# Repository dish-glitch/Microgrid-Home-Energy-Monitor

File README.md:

# Home Energy Monitor

**A custom PCB that measures real-time household power consumption (Watts, apparent power (VA), and power factor) and streams live data to an OLED screen, a WiFi dashboard, and a Modbus TCP/IP server (the same protocol real industrial power meters use).**

---

## Schematic Preview

---

## PCB Preview

## Enclosure Preview

---

## What It Does

Non-invasive current transformer (CT) sensors clip around household wires inside a breaker box(does not touch any live wires). The custom PCB conditions the signal from the sensors and feeds it to an ESP32 microcontroller. The microcontroller then samples the voltage and current to compute:

- **Real Power (Watts)** 
- **Apparent Power (VA)**
- **Power Factor** 
- **Cumulative kWh** 

The readings come out three ways: a small OLED on the device, a live dashboard served over WiFi that you can open in any browser, and a Modbus TCP/IP server so industrial software like PLCs, SCADA, or Home Assistant can read the meter directly.

---

## How It Works

The SCT-013 current clamp outputs a small AC signal that mirrors the current in the wire it's clamped around. Before the ESP-32 is able to sample the signal, it must condition it. 

1. **It swings negative** — the ESP32 ADC only reads 0–3.3V. An op-amp bias circuit lifts the signal to a 1.65V midpoint so it never goes below 0V.
2. **It's in the wrong units** — a burden resistor converts current to a readable voltage via Ohm's Law (V = I × R).
3. **It carries noise** — an RC low-pass filter passes 60Hz but blocks high-frequency interference.

The ESP32 samples the signal and calculates RMS values in firmware and then uses those measurements to produce real power, apparent power, and power factor. 

---

## Modbus TCP/IP

I added a Modbus TCP server so this works more like a real industrial power meter instead of just a hobby project. Modbus is the protocol that commercial meters from companies like Schneider Electric and ABB use to send their readings to building systems and SCADA software. I got the idea from a PLC Dojo certification I finished on programming Modbus TCP clients and servers, and I wanted to actually use what I learned on my own hardware.

The ESP32 runs the Modbus server on port 502 at the same time as the web dashboard on port 80, so both run off the same WiFi. Any Modbus client, like a PLC, SCADA software, Home Assistant, Node-RED, or even a Python script, can read the meter by asking for its holding registers with Function Code 3.

Modbus registers can only hold 16-bit whole numbers, so I scale the decimal readings into whole numbers before writing them, and the client divides by the same number to get the real value back.

| Register | Modbus Address | Value | Scaling | Example |
|---|---|---|---|---|
| 0 | 40001 | Voltage (Vrms) | ×10 | `1200` → 120.0 V |
| 1 | 40002 | Current CH1 (Irms) | ×100 | `500` → 5.00 A |
| 2 | 40003 | Real Power CH1 (W) | ×1 | `600` → 600 W |
| 3 | 40004 | Apparent Power CH1 (VA) | ×1 | `650` → 650 VA |
| 4 | 40005 | Power Factor | ×100 | `92` → 0.92 |
| 5 | 40006 | Total Energy (kWh) | ×10 | `123` → 12.3 kWh |
| 6 | 40007 | Current CH2 (Irms) | ×100 | `300` → 3.00 A |
| 7 | 40008 | Real Power CH2 (W) | ×1 | `360` → 360 W |

> Register 0 in the code shows up as 40001 in most Modbus software. The 4xxxx numbering is just the standard way holding registers get labeled.

---

## Hardware

> Prices are what you actually pay per order, not per component. Amazon prices fluctuate — check links for current pricing. Order DigiKey items together to share one shipping fee (~$8 flat).

| Component | Ref | Need | What to Buy | Pack | Est. Order Price | Where |
|---|---|---|---|---|---|---|
| ESP32-WROOM-32 module | U1 | 1 | ESP-WROOM-32D 5-pack | 5 | ~$16 | [Amazon][(https://www.amazon.com/ESP-WROOM-32D-ESP-32-Bluetooth-Module-ESP32-WROOM-32D/dp/B085BNHPW5)](https://www.amazon.com/DORHEA-ESP-WROOM-32D-Bluetooth-integrates-ESP32-D0WD/dp/B08XXH9RMT/ref=sr_1_4?crid=1PAA57ZDBXXKA&dib=eyJ2IjoiMSJ9._MntEg_yRxGkBw1EfxLq6cc-w3Tk4YEgtB1QtlP6Z4yxtTF4Fgfk1zGfVmxLEI5m1rj4c-1jFTGRVePtGjaZB-u8IC_M2NuE5i72-Z6dyDMhy--t0tJ7uNgECgIogId0cCfDd5HPa67FyROcsTOtQSfSzK0LDP2i9msGrrE8LXcygPlws7SA2oZ1K6vlKAqsIRbaACC8jXyDBxBi5YwBBB_2cBgjYlD-LvbD8llQCdCVJK7sxuom2wjza4DP2pI0dcSs2QY-L5haReDtaOngVqGGzxCfWKOjql3sHXlfzxA.qUdqsXgRGlyqVaLIAANpF-NeytYFG2HdsdXi1yK_r4c&dib_tag=se&keywords=ESP-WROOM-32D%2BESP32%2B2.4GHz%2BDual-Mode%2BBluetooth%2Band%2BWiFi%2BLow%2BPower%2BModule&nsdOptOutParam=true&qid=1783296447&s=electronics&sprefix=esp-wroom-32d%2Besp32%2B2.4ghz%2Bdual-mode%2Bbluetooth%2Band%2Bwifi%2Blow%2Bpower%2Bmodule%2Celectronics%2C220&sr=1-4&th=1) |
| CT sensor SCT-013-000 (100A) | J1, J2 sensors | 2 | KOOBOOK 2-pack | 2 | ~$15 | [Amazon](https://www.amazon.com/KOOBOOK-SCT-013-000-Non-invasive-Current-Transformer/dp/B07S4G2Y27) |
| ZMPT101B voltage sensor module | J6 sensor | 1 | Single module | 1 | ~$8 | Amazon |
| Op-amp MCP6002 DIP-8 | U2 | 1 | Juried Engineering 1-pack | 1 | ~$4 | [Amazon](https://www.amazon.com/MICROCHIP-MCP6002-I-MCP6002-Operational-Amplifier/dp/B07GMWJ523) |
| Voltage regulator AMS1117-3.3 | U3 | 1 | 10-pack SOT-223 | 10 | ~$6 | [Amazon](https://www.amazon.com/AMS1117-3-3-LM1117-SOT-223-Voltage-Regulator/dp/B00Y5EKAU2) |
| SMD resistors 0603 (33Ω, 10kΩ, 4.7kΩ, 5.1kΩ, 150Ω) | R1–R14 | 14 total | 0603 assortment kit — covers all 5 values | 660pc / 33 values | ~$9 | [Amazon](https://www.amazon.com/660pcs-0603-Resistors-Assortment-Values/dp/B0CH2XD7JY) |
| SMD capacitors 0603+0805 (100nF, 10µF) | C1–C9 | 9 total | 0603/0805 assortment kit (10pF–22µF) | 960pc / 16 values | ~$10 | [Amazon](https://www.amazon.com/Capacitor-10pF-22uF-Multilayer-Capacitors-Assortment/dp/B094Z9V5KK) |
| 3.5mm audio jack SMT (CUI SJ-3523-SMT) | J1, J2 | 2 | Order 2 individually | 2 | ~$5 | [DigiKey](https://www.digikey.com/en/products/detail/same-sky-formerly-cui-devices/SJ-3523-SMT-TR/281297) |
| USB-C receptacle (GCT USB4085-GF-A) — optional, the board can be powered from a 5V bench supply | J4 | 1 | Order 1 individually | 1 | ~$1 | [DigiKey](https://www.digikey.com/en/products/detail/gct/USB4085-GF-A/9859662) |
| 3mm LED (red or green) | D1, D2 | 2 | 10-pack | 10 | ~$5 | [Amazon](https://www.amazon.com/3mm-Round-Top-Red-LED/dp/B017TR4XWW) |
| Tactile button 6×6×4.3mm THT | SW1, SW2 | 2 | 10-pack | 10 | ~$5 | [Amazon](https://www.amazon.com/6x6x4-3mm-Momentary-Tactile-Button-Through/dp/B00EDJYK46) |
| 2.54mm male pin headers (J3 4-pin, J5 6-pin, J6 3-pin) | J3, J5, J6 | 13 pins | 40-pin breakable strip (snap to length) | 10×40 strips | ~$6 | [Amazon](https://www.amazon.com/MCIGICM-Header-2-45mm-Arduino-Connector/dp/B07PKKY8BX) |
| SSD1306 OLED 0.96" I2C | J3 display | 1 | Single unit | 1 | ~$7 | [Amazon](https://www.amazon.com/SSD1306-Display-128x64-Driver-Screen/dp/B0GRGLP6WW) |
| CP2102 USB-to-UART programmer (to flash via J5) | — | 1 | HiLetgo CP2102 | 1 | ~$7 | [Amazon](https://www.amazon.com/HiLetgo-CP2102-Converter-Adapter-Downloader/dp/B00LODGRV8) |
| PCB fabrication | — | 1 run | JLCPCB 5 boards + shipping | 5 boards | ~$20 | [JLCPCB](https://jlcpcb.com) |
| Enclosure | — | 1 | 3D printed PETG-CF | — | $0 | filament on hand |
| DigiKey shipping | — | — | Flat rate (order SJ-3523 + USB4085 together) | — | ~$8 | — |
| **Total** | | | | | **~$132** | |

---

## Repository Structure

```
home-energy-monitor/
├── hardware/        # KiCad schematic, PCB layout, Gerber files
├── firmware/        # ESP32 Arduino code (energy-monitor + board-test bring-up sketch)
├── enclosure/       # FreeCAD source + STL files for 3D printing
└── docs/
    └── photos/      # Build progress photos
```

---

## Build Log

| Date | Milestone |
|---|---|
| June 10, 2026 | Project started. Repository initialized. |
| June 11, 2026 | KiCad schematic started — analog front-end both CT channels complete |
| June 13, 2026 | KiCad schematic complete — ERC passes clean, all components wired |
| June 14, 2026 | PCB layout complete — all components placed, routed, ground plane poured, DRC clean |
| June 14, 2026 | Gerbers exported and committed — ready for JLCPCB upload |
| June 14, 2026 | Firmware written — RMS sampling, power math, OLED display, kWh accumulator. Verified on Wokwi simulator. |
| June 15, 2026 | WiFi dashboard complete — ESP32 serves live readings over HTTP, JavaScript polls every second |
| June 16, 2026 | 3D enclosure designed by [@hummos430](https://github.com/hummos430) in Fusion 360 — files committed |
| June 16, 2026 | Stardance funding submitted — S tier $150 |
| July 3, 2026 | DRC audit fixes — solid B.Cu ground plane added, ESP32 thermal via drills fixed, USB-C clearance rule corrected. ERC + DRC verified 0 errors. Gerbers re-exported — board ready to order |
| July 8, 2026 | Modbus TCP/IP server added — ESP32 exposes 8 holding registers on port 502, runs alongside the web dashboard |
| — | PCBs ordered from JLCPCB and received |
| Oct 22, 2026 | Board assembly started — SMD parts with solder paste on a mini hot plate, THT by hand |
| Oct 23, 2026 | First power-up. Tracked a 3.3V rail "short" down to 10Ω resistors (marked `01X`) fitted where the 10kΩ bias resistors (`01C`) belong — replaced them, rail came up at 3.3V. ESP32 boots and flashes over the J5 header |
| Oct 28, 2026 | Op-amp replaced (bench-tested on a breadboard first) and a bodge wire added for a damaged U2 pin 5 pad. Both CT channels verified at the 1.65V bias point, OLED found on I2C, full firmware running on the board |
| Nov 10, 2026 | CT jacks fitted (plug bodies trimmed to clear the PCB). First real current measurements with `SIMULATION 0`: a 300 W rice cooker read **2.40 A** on Cook against 2.50 A expected (300 W ÷ 120 V), within 4% before calibration. ICAL tuned 60.6 → 63.1. A desk fan read ~0.2 A; the noise floor with nothing on is ~0.12 A |
| — | ZMPT101B mains side enclosed, VCAL calibrated, real watts + power factor |
| — | Dashboard live, full system working |

---

## Build Photos

The assembled board running the real firmware (still in `SIMULATION 1` mode until the CT jacks and voltage sensor are connected) — OLED live, power LED and status LED on:

| First power-up | 5V bench supply, constant-voltage mode |
|---|---|
|  |  |

**Bring-up test** ([`firmware/board-test`](firmware/board-test/board-test.ino)) — the OLED answers on I2C, and both CT channels sit at the 1.65V bias midpoint with no clamp plugged in:

WiFi dashboard served by the ESP32 (port 80), viewed in a laptop browser on the same network:

Modbus TCP read from a laptop using [`tools/modbus_read.py`](tools/modbus_read.py) (Function Code 3, holding registers 40001–40008):

```
Raw registers: (1200, 500, 550, 600, 92, 0, 300, 360)
----------------------------------
Voltage:         120.0 V
Current CH1:     5.00 A
Real Power CH1:  550 W
Apparent CH1:    600 VA
Power Factor:    0.92
Total Energy:    0.0 kWh
Current CH2:     3.00 A
Real Power CH2:  360 W
```

*(Total energy is stored ×10, so it reads 0.0 until the running total passes 0.1 kWh.)*

Firmware serial output — readings every loop, kWh accumulating:

ESP32 boot log over the J5 programming header:

---

## Simulation

Test the firmware logic without hardware — runs in browser:

Simulates dual CT sensor readings, RMS power math, serial output, and OLED display on a virtual ESP32. CH1 uses test values (120V, 5A, 550W, PF 0.92) to verify the signal chain and kWh accumulator logic.

---

## Status

- [x] KiCad schematic — ERC clean (0 errors)
- [x] PCB layout — DRC clean (0 violations, 0 unconnected); B.Cu ground plane added
- [x] Gerbers exported from the DRC-clean board — ready for JLCPCB upload
- [x] Firmware — ADC sampling + RMS math
- [x] Firmware — power factor calculation
- [x] PCB fabrication (JLCPCB)
- [x] Board assembly + bring-up — power, ESP32, both CT channels, OLED verified
- [x] 3D enclosure design
- [x] WiFi dashboard
- [x] Modbus TCP/IP server (8 holding registers, Function Code 3)
- [x] CT jacks (J1/J2) fitted
- [x] Current calibration (ICAL) against a known resistive load
- [ ] ZMPT101B mains side enclosed + voltage calibration (VCAL)
- [ ] Full system test

---

## Acknowledgements

- **[@hummos430](https://github.com/hummos430)** — Designed and 3D printed the enclosure in Fusion 360
- **[Claude (Anthropic)](https://claude.ai)** — Claude was used to help document this project. I often recorded voice notes describing my engineering ideas, design decisions, and progress, then used Claude to organize those notes into structured GitHub documentation and tables. It also helped review the BOM and sanity-check component selections for consistency. The schematic, PCB layout, firmware, testing, and engineering decisions are my own.

---

## License

MIT — use, modify, share freely. See [LICENSE](LICENSE).

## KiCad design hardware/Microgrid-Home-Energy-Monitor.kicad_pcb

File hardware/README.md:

# Hardware

Custom 2-layer PCB designed in KiCad 9. Measures real-time household power consumption using non-invasive current transformer sensors.

---

## PCB Specifications

| Spec | Value |
|---|---|
| Layers | 2 (F.Cu / B.Cu) |
| Board dimensions | ~130mm × 75mm |
| Min trace width | 0.2mm signal / 0.4mm power |
| Min clearance | 0.15mm (accommodates the USB-C footprint's pad spacing; JLCPCB handles down to 0.127mm) |
| Copper pour | GND flood on F.Cu + solid GND plane on B.Cu, joined by stitching vias |
| Via drill | 0.3mm min |
| Surface finish | HASL (lead-free) |
| Fabrication | JLCPCB |

---

## Design Overview

### Power Path
USB-C (5V VBUS) → AMS1117-3.3 linear regulator → 3.3V rail → ESP32 + all peripherals

CC1 and CC2 resistors (5.1kΩ to GND) identify the board as a USB device to the host charger, enabling 5V/500mA delivery per USB-C spec.

### CT Sensor Signal Conditioning (per channel)
Each channel processes the AC output of an SCT-013-000 current transformer:

```
SCT-013 → 33Ω burden resistor → 10µF coupling cap → MCP6002 op-amp buffer → ESP32 ADC
                                    ↑
                          10kΩ/10kΩ bias divider (1.65V midpoint)
```

1. **Burden resistor (33Ω):** The SCT-013 outputs a small currecnt but the ESP32 measures the voltage. The 33 ohm burden resisotr converts that currecnt into a voltage using Ohm's law. At the senors's max rated current, this produeces 1.65 V RMS 2.33 V peak. 

2. **Bias divider (2× 10kΩ):** Becuase the ESP32 ADC can't read negative voltages, 2 10k ohm resistors create a 1.65 V bais point.
3. **Coupling capacitor (10µF):** Blocks DC from the burden resistor, and passes the 60Hz AC signal.
4. **MCP6002 buffer:** Unity-gain op-amp buffer to keep the bais network independent from the ESP32 ADC. Its high imput impedance prevents the bais voltage from shifting. 

### Voltage Sensing
ZMPT101B voltage transformer connects to J6. its output is routed to GPIO36 which is an input-only ADC pin with no internal pull resistors, chosen to minimize noise on the analog signal.

### I2C Bus
SDA (GPIO21) and SCL (GPIO22) pulled up to 3.3V via 4.7kΩ resistors. Pull-up value chosen for standard-mode I2C (100 kHz) with expected bus capacitance under 50pF.

### ESP32 Boot Circuit
- EN pulled high via 10kΩ (R7) + 100nF to GND for clean power-on reset
- GPIO0 held high by the ESP32's internal pull-up; SW2 pulls GPIO0 low for bootloader entry (R10 was meant as an external pull-up, but rev 1 wires it EN ↔ GPIO0 — leave it unfitted, see Assembly Notes)
- SW1 pulls EN low for hard reset

---

## Schematic

See [`Microgrid-Home-Energy-Monitor.kicad_sch`](Microgrid-Home-Energy-Monitor.kicad_sch)

---

## PCB Layout

See [`Microgrid-Home-Energy-Monitor.kicad_pcb`](Microgrid-Home-Energy-Monitor.kicad_pcb)

Key layout decisions:
- Analog front-end (J1, J2, U2, bias resistors) grouped bottom-right, away from ESP32 WiFi antenna
- ESP32 antenna overhangs the keepout zone — no copper pour under antenna area
- AMS1117 decoupling caps (C3–C6) placed within 2mm of regulator pins
- ESP32 VDD decoupling (C7, C8) placed directly below VDD pin
- USB-C connector (J4) edge-mounted on right wall for direct cable access
- Ground pour floods entire F.Cu layer

---

## Bill of Materials

| Ref | Component | Value | Package | MPN | Supplier |
|---|---|---|---|---|---|
| U1 | ESP32-WROOM-32 | — | Module | ESP32-WROOM-32E-N4 | Mouser 356-ESP32WROOM32EN4 |
| U2 | MCP6002 Op-Amp | — | DIP-8 | MCP6002-I/P | Digikey MCP6002-I/P-ND |
| U3 | AMS1117-3.3 | 3.3V LDO | SOT-223 | AMS1117-3.3 | Digikey 1665-1016-1-ND |
| J1, J2 | CT Sensor Input | 3.5mm jack | SMD | SJ-3523-SMT | Digikey CP-3523SJCT-ND |
| J3 | OLED Connector | 4-pin | 2.54mm header | — | generic |
| J4 | USB-C Receptacle (optional, see notes) | USB 2.0 | THT 16P | GCT USB4085-GF-A | Digikey 2073-USB4085-GF-ACT-ND |
| J5 | Programming Header | 6-pin | 2.54mm header | — | generic |
| J6 | ZMPT101B Connector | 3-pin | 2.54mm header | — | generic |
| R1, R4 | Burden Resistor (CH1, CH2) | 33Ω 1% | 0603 | — | generic |
| R2, R3, R5, R6 | Bias Resistor (R2/R3 CH1, R5/R6 CH2) | 10kΩ | 0603 | — | generic |
| R7 | EN Pull-up | 10kΩ | 0603 | — | generic |
| R8, R9 | I2C Pull-up | 4.7kΩ | 0603 | — | generic |
| R10 | GPIO0 Pull-up — **do not fit on rev 1**, see notes | 10kΩ | 0603 | — | generic |
| R11, R12 | CC Pull-down (only needed with J4) | 5.1kΩ | 0603 | — | generic |
| R13, R14 | LED Current Limit | 150Ω | 0603 | — | generic |
| C1, C2 | Coupling Cap | 10µF | 0805 | — | generic |
| C3, C6 | LDO Bulk Cap | 10µF | 0805 | — | generic |
| C4, C5 | LDO Bypass Cap | 100nF | 0603 | — | generic |
| C7 | ESP32 Bypass | 100nF | 0603 | — | generic |
| C8 | ESP32 Bulk | 10µF | 0805 | — | generic |
| C9 | EN Filter Cap | 100nF | 0603 | — | generic |
| D1 | Power LED | Red | 3mm THT | — | generic |
| D2 | Status LED | Green | 3mm THT | — | generic |
| SW1 | Reset Button | — | 6mm THT | — | generic |
| SW2 | Boot Button | — | 6mm THT | — | generic |
| CT1, CT2 | CT Sensor | SCT-013-000 | Clamp | SCT-013-000 | Amazon/AliExpress |
| VT1 | Voltage Sensor Module (plugs into J6) | ZMPT101B | Module | ZMPT101B | Amazon/AliExpress |

---

## Assembly Notes (rev 1)

Lessons from assembling the first board (solder paste + hot plate for SMD, iron for THT):

- **Read the 0603 resistor markings.** The 10kΩ bias resistors are marked **`01C`** (EIA-96) or **`103`**. A part marked **`01X`** is **10Ω** — fitting those in R2/R3/R5/R6 puts two 20Ω paths across the 3.3V rail and looks exactly like a short (supply drops into CC, the resistors near U2 get warm).
- **R10 — do not fit.** The BOM calls it a GPIO0 pull-up, but on the rev 1 PCB it is wired **EN ↔ GPIO0**, which drags GPIO0 low whenever RESET is pressed and can drop the ESP32 into download mode. The ESP32's internal pull-up on GPIO0 is enough, and SW2 still pulls it low to flash. *Fix for rev 2: connect R10 between GPIO0 and +3.3V.*
- **J1/J2 sit too far in from the board edge.** The SCT-013's molded plug body hits the PCB before the plug seats fully, and the plug's metal collar scrapes the solder mask in front of each jack. On rev 1, trim about 1–2 mm off the underside of each plug body (sandpaper or a file, not a soldering iron), seal any exposed wire with nail polish or CA glue, and protect the board in front of the jacks with Kapton tape. *Fix for rev 2: move J1/J2 so their openings are flush with, or slightly past, the board edge.*
- **J2 is CH1 and J1 is CH2.** J2 feeds R1/C1 → GPIO34 (`PIN_CT1`, real power + PF), J1 feeds R4/C2 → GPIO35 (`PIN_CT2`). Plug the clamp for the main load into **J2**.
- **J4 (USB-C) is optional.** It is power-only (D+/D− are not connected). Without it, power the board from a 5V bench supply into the J4 **VBUS** and **GND** holes or **TP1 (VBUS) / TP3 (GND)**, and leave R11/R12 off. In each J4 row the outermost small hole is GND and the next one in is VBUS; the four large oval slots are the shield and are **not** connected.
- **U2 orientation:** pin 1 is the **square pad**, at the notch end next to **TP2**. A socket is worth it — the chip is easy to damage when desoldering.
- **Do the SMD reflow before any THT parts** — headers, buttons and LEDs have plastic that will not survive the hot plate.
- **Programming:** J5 needs only 3 wires to a CP2102 — GND→pin 1, TXD→pin 4 (RX0), RXD→pin 3 (TX0). Leave the adapter's 3V3/5V unconnected when the board has its own supply. There is no auto-reset circuit: hold **BOOT (SW2)**, tap **RESET (SW1)**, release BOOT, upload, then press RESET.
- **OLED pin order:** many SSD1306 modules are **GND, VCC, SCL, SDA**, while J3 is **3.3V, GND, SCL, SDA**. Wire by label with jumpers instead of plugging the module straight in.

### Bring-up checklist

| Check | Expected |
|---|---|
| TP2 (3.3V) ↔ TP3 (GND), continuity, unpowered | **No beep** |
| 5V supply, ESP32 with factory firmware | CV, ~0.11 A, D1 lit |
| TP2 | 3.3V |
| [`board-test`](../firmware/board-test/board-test.ino) sketch, no sensors connected | CT1 ≈ CT2 ≈ **1650 mV** (bias midpoint), D2 blinking, BOOT button reported |
| OLED on J3 | I2C scan finds **0x3C** |

---

## Design Verification

All fixes from the 2026-07-02 DRC audit are complete (verified with `kicad-cli`):

- **ERC: 0 errors.** **DRC: 0 violations, 0 unconnected items.**
- GND split-pour islands eliminated by adding a solid B.Cu ground plane with stitching
  vias — front pour fragments all tie to it, so pinch-offs can't strand a ground pin
- ESP32 thermal vias enlarged to 0.3mm drill (JLCPCB 2-layer minimum)
- Minimum clearance set to 0.15mm to fit the USB-C footprint's actual pad spacing

---

## Fabrication Files

Gerber files for JLCPCB are in [`gerbers/`](gerbers/) — exported from the DRC-clean board, **ready to upload**.

JLCPCB order settings:
- Layers: 2
- Dimensions: per gerber
- PCB Qty: 5
- PCB Color: Black
- Surface Finish: HASL(lead-free)
- Copper Weight: 1oz
- All other settings: default

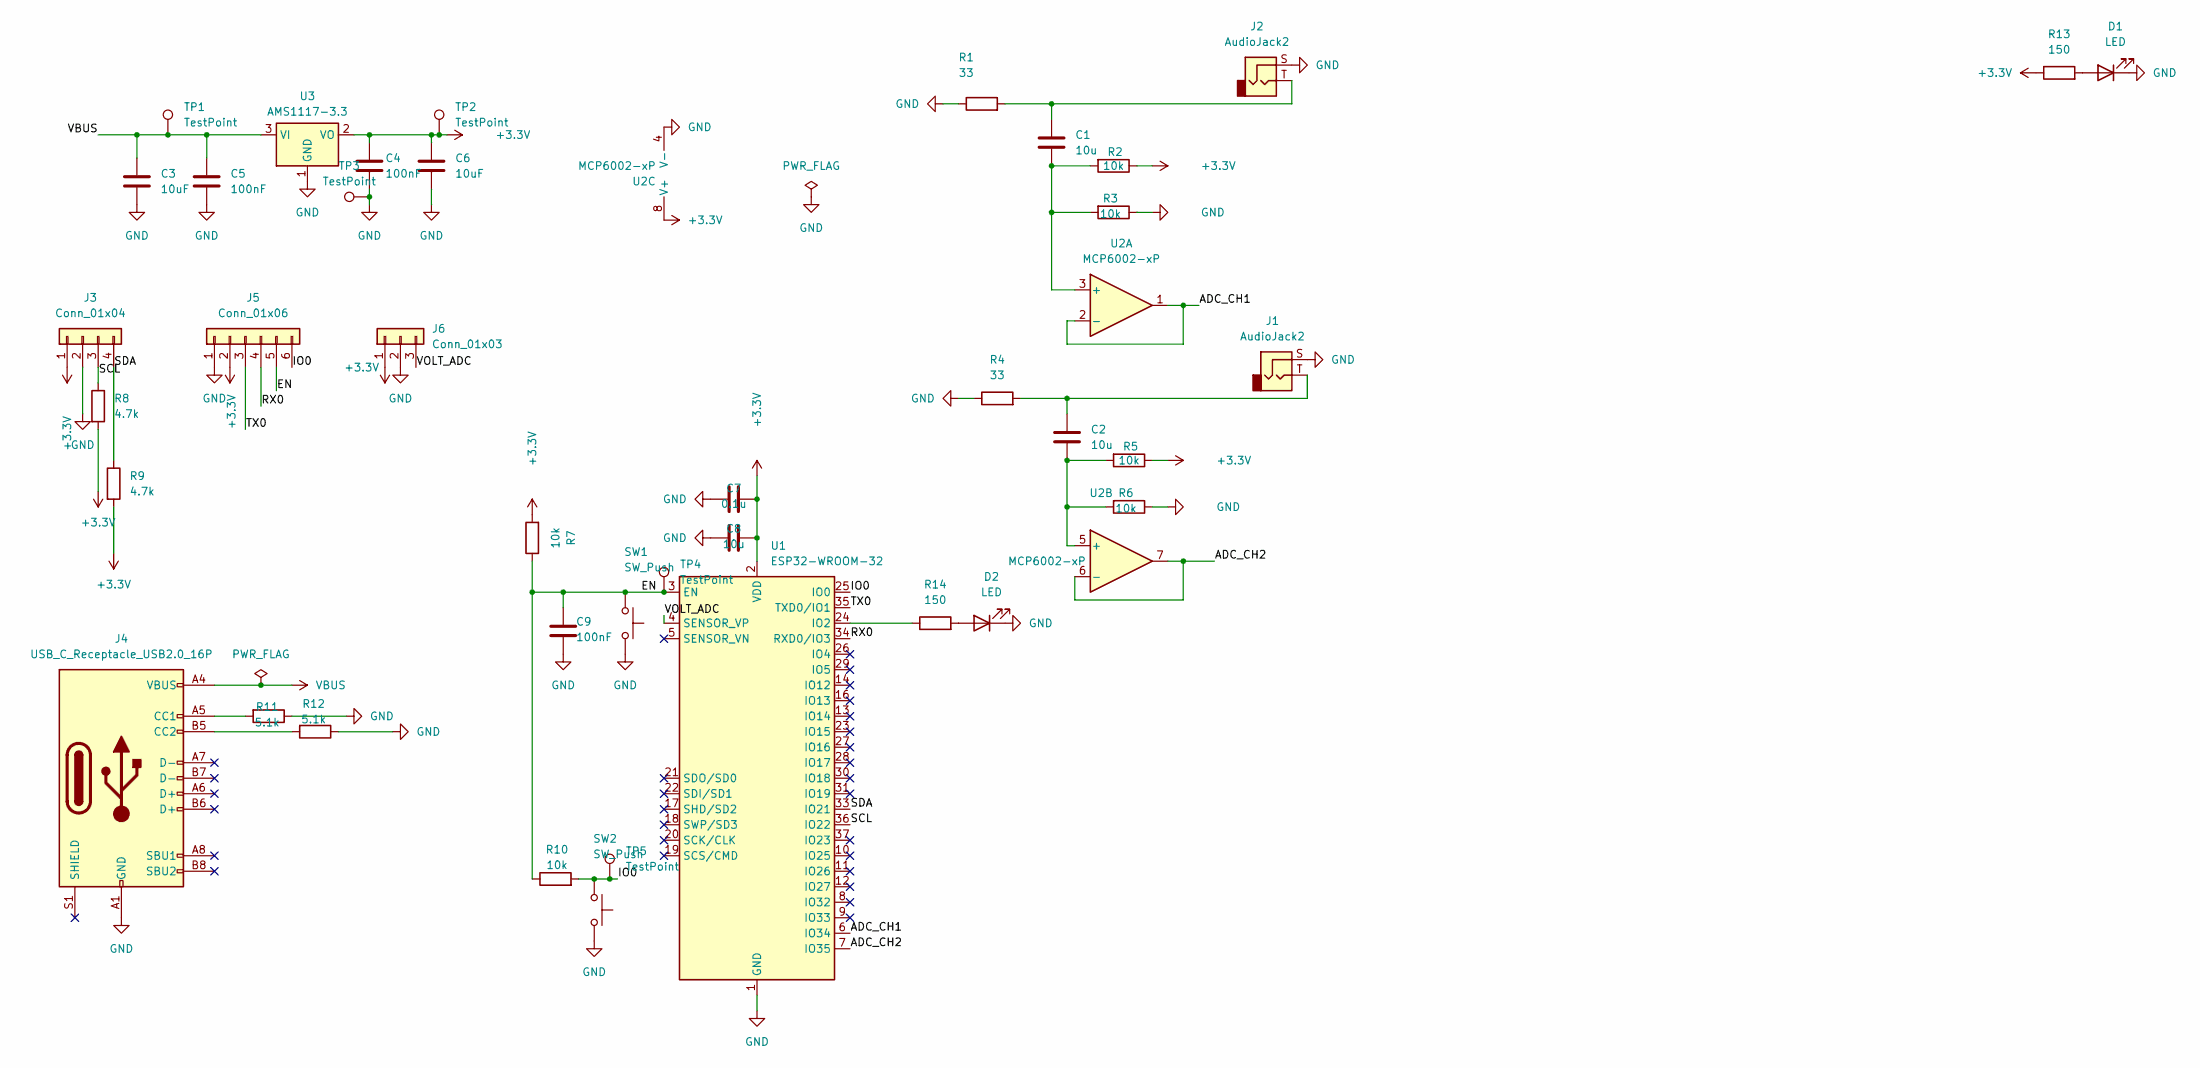
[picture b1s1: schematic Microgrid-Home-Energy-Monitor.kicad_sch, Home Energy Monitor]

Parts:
C1, C2, C8: 10u; C_0805_2012Metric
C3, C6: 10uF; C_0805_2012Metric
C4, C5, C9: 100nF; C_0603_1608Metric
C7: 0.1u; C_0603_1608Metric
D1, D2: LED; LED_D3.0mm
J1, J2: AudioJack2; Jack_3.5mm_CUI_SJ-3523-SMT_Horizontal
J3: Conn_01x04; PinHeader_1x04_P2.54mm_Vertical
J4: USB_C_Receptacle_USB2.0_16P; USB_C_Receptacle_GCT_USB4085
J5: Conn_01x06; PinHeader_1x06_P2.54mm_Vertical
J6: Conn_01x03; PinHeader_1x03_P2.54mm_Vertical
R1, R4: 33; R_0603_1608Metric
R2, R3, R5, R6, R7, R10: 10k; R_0603_1608Metric
R8, R9: 4.7k; R_0603_1608Metric
R11, R12: 5.1k; R_0603_1608Metric
R13, R14: 150; R_0603_1608Metric
SW1, SW2: SW_Push; SW_PUSH_6mm_H4.3mm
TP1, TP2, TP3, TP4, TP5: TestPoint; TestPoint_Pad_D1.5mm
U1: ESP32-WROOM-32
U2: MCP6002-xP; DIP-8_W7.62mm
U3: AMS1117-3.3; SOT-223-3_TabPin2

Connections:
+3.3V: C4.1, C6.1, C7.2, C8.2, J3.1, J5.2, J6.1, R2.1, R5.1, R7.2, R8.2, R9.2, R13.1, TP2.1, U1.2 (VDD), U2.8 (V+), U3.2 (VO)
/ADC_CH1: U1.6 (IO34), U2.1, U2.2 (-)
/ADC_CH2: U1.7 (IO35), U2.6 (-), U2.7
/EN: C9.1, J5.5, R7.1, R10.1, SW1.1, TP4.1, U1.3 (EN)
/IO0: J5.6, R10.2, SW2.1, TP5.1, U1.25 (IO0)
/RX0: J5.4, U1.34 (RXD0/IO3)
/SCL: J3.3, R8.1, U1.36 (IO22)
/SDA: J3.4, R9.1, U1.33 (IO21)
/TX0: J5.3, U1.35 (TXD0/IO1)
/VOLT_ADC: J6.3, U1.4 (SENSOR_VP)
GND: C3.2, C4.2, C5.2, C6.2, C7.1, C8.1, C9.2, D1.1 (K), D2.1 (K), J1.S, J2.S, J3.2, J4.A1 (GND), J4.A12 (GND), J4.B1 (GND), J4.B12 (GND), J5.1, J6.2, R1.1, R3.1, R4.1, R6.1, R11.1, R12.1, SW1.2, SW2.2, TP3.1, U1.1 (GND), U1.15 (GND), U1.38 (GND), U1.39 (GND), U2.4 (V-), U3.1 (GND)
unnamed: C1.1, J2.T, R1.2
unnamed: C2.1, J1.T, R4.2
unnamed: D1.2 (A), R13.2
unnamed: D2.2 (A), R14.2
unnamed: J4.A5 (CC1), R11.2
unnamed: J4.B5 (CC2), R12.2
unnamed: R14.1, U1.24 (IO2)
unnamed: C1.2, R2.2, R3.2, U2.3 (+)
unnamed: C2.2, R5.2, R6.2, U2.5 (+)
VBUS: C3.1, C5.1, J4.A4 (VBUS), J4.A9 (VBUS), J4.B4 (VBUS), J4.B9 (VBUS), TP1.1, U3.3 (VI)

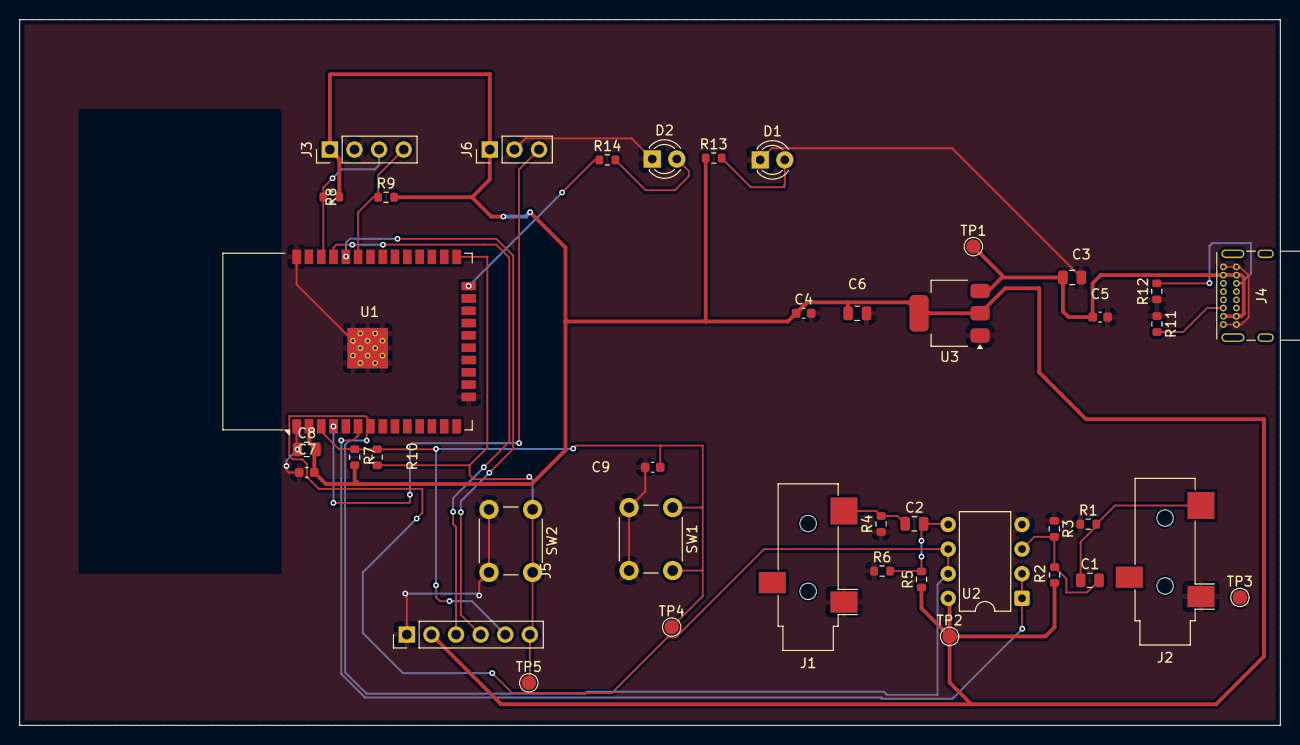
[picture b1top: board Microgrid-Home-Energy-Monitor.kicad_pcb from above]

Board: 2 copper layers, 130.2 x 72.9 mm, 41 parts (0 on the bottom side), 21 nets.

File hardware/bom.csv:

Reference,Component,Value,Package,MPN,Qty,Est Unit Cost (USD),Supplier
U1,ESP32-WROOM-32,,Module,ESP32-WROOM-32E-N4,1,$4.00,Mouser
U2,MCP6002 Op-Amp,,DIP-8,MCP6002-I/P,1,$0.50,Digikey
U3,AMS1117-3.3,3.3V LDO,SOT-223,AMS1117-3.3,1,$0.35,Digikey
J1,CT Sensor Jack,3.5mm stereo,SMD,SJ-3523-SMT,1,$0.60,Digikey
J2,CT Sensor Jack,3.5mm stereo,SMD,SJ-3523-SMT,1,$0.60,Digikey
J3,OLED Connector,4-pin 2.54mm,THT header,,1,$0.10,generic
J4,USB-C Receptacle,USB 2.0 16P,SMD,GCT USB4085-GF-A,1,$0.85,Digikey
J5,Programming Header,6-pin 2.54mm,THT header,,1,$0.10,generic
J6,ZMPT101B Connector,3-pin 2.54mm,THT header,,1,$0.10,generic
R1,Burden Resistor,33Ω 1%,0603,,1,$0.05,generic
R2,Burden Resistor,33Ω 1%,0603,,1,$0.05,generic
R3,Bias Resistor,10kΩ,0603,,1,$0.02,generic
R4,Bias Resistor,10kΩ,0603,,1,$0.02,generic
R5,Bias Resistor,10kΩ,0603,,1,$0.02,generic
R6,Bias Resistor,10kΩ,0603,,1,$0.02,generic
R7,EN Pull-up,10kΩ,0603,,1,$0.02,generic
R8,I2C Pull-up SDA,4.7kΩ,0603,,1,$0.02,generic
R9,I2C Pull-up SCL,4.7kΩ,0603,,1,$0.02,generic
R10,GPIO0 Pull-up,10kΩ,0603,,1,$0.02,generic
R11,CC1 Pull-down,5.1kΩ,0603,,1,$0.02,generic
R12,CC2 Pull-down,5.1kΩ,0603,,1,$0.02,generic
R13,LED Resistor D1,150Ω,0603,,1,$0.02,generic
R14,LED Resistor D2,150Ω,0603,,1,$0.02,generic
C1,Coupling Cap CH1,10µF,0805,,1,$0.10,generic
C2,Coupling Cap CH2,10µF,0805,,1,$0.10,generic
C3,LDO Input Bulk,10µF,0805,,1,$0.10,generic
C4,LDO Output Bypass,100nF,0603,,1,$0.05,generic
C5,LDO Input Bypass,100nF,0603,,1,$0.05,generic
C6,LDO Output Bulk,10µF,0805,,1,$0.10,generic
C7,ESP32 VDD Bypass,100nF,0603,,1,$0.05,generic
C8,ESP32 VDD Bulk,10µF,0805,,1,$0.10,generic
C9,EN Filter Cap,100nF,0603,,1,$0.05,generic
D1,Power LED,Red 5mm,THT,,1,$0.10,generic
D2,Status LED,Green 5mm,THT,,1,$0.10,generic
SW1,Reset Button,6mm,THT,,1,$0.15,generic
SW2,Boot Button,6mm,THT,,1,$0.15,generic
CT1,CT Sensor,SCT-013-000 100A,Clamp,SCT-013-000,1,$7.00,Amazon
CT2,CT Sensor,SCT-013-000 100A,Clamp,SCT-013-000,1,$7.00,Amazon
VT1,Voltage Sensor Module (plugs into J6),ZMPT101B,Module,ZMPT101B,1,$8.00,Amazon
,,,,PCB Fabrication (JLCPCB 5x),,,$20.00,JLCPCB
,,,,TOTAL,,,~$50.00,

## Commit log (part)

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2026-06-10 Add project structure, professional README, and build log
2026-06-12 add KiCad schematic — analog front-end both CT channels
2026-06-12 update README — fix burden resistor value, add build log entry
2026-06-12 add OLED connector, USB-C power input, AMS1117 regulator, decoupling caps
2026-06-12 complete schematic — ERC clean, all components wired
2026-06-12 complete schematic, add schematic screenshots to README
2026-06-13 Complete schematic fixes: USB-C, decoupling caps, boot/reset buttons, I2C pullups, programming header, ZMPT101B connector
2026-06-14 Complete PCB layout and routing - DRC clean
2026-06-14 Update README — PCB layout complete, fix build log
2026-06-14 Add professional hardware docs, BOM, design decisions, gerber instructions
